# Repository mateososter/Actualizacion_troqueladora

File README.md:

# Actualizacion_troqueladora

Repositorio para la realizacion del proyecto para actualizar una troqueladora manual de mandibulas, agregando un display e identificación 
de usuarios por el método de tarjetas RFID.

Entorno a utilizar:   Keil uVision 5
Asistente:            CubeMX
Lenguaje principal:   c
Placa de desarrollo:  STM32F411

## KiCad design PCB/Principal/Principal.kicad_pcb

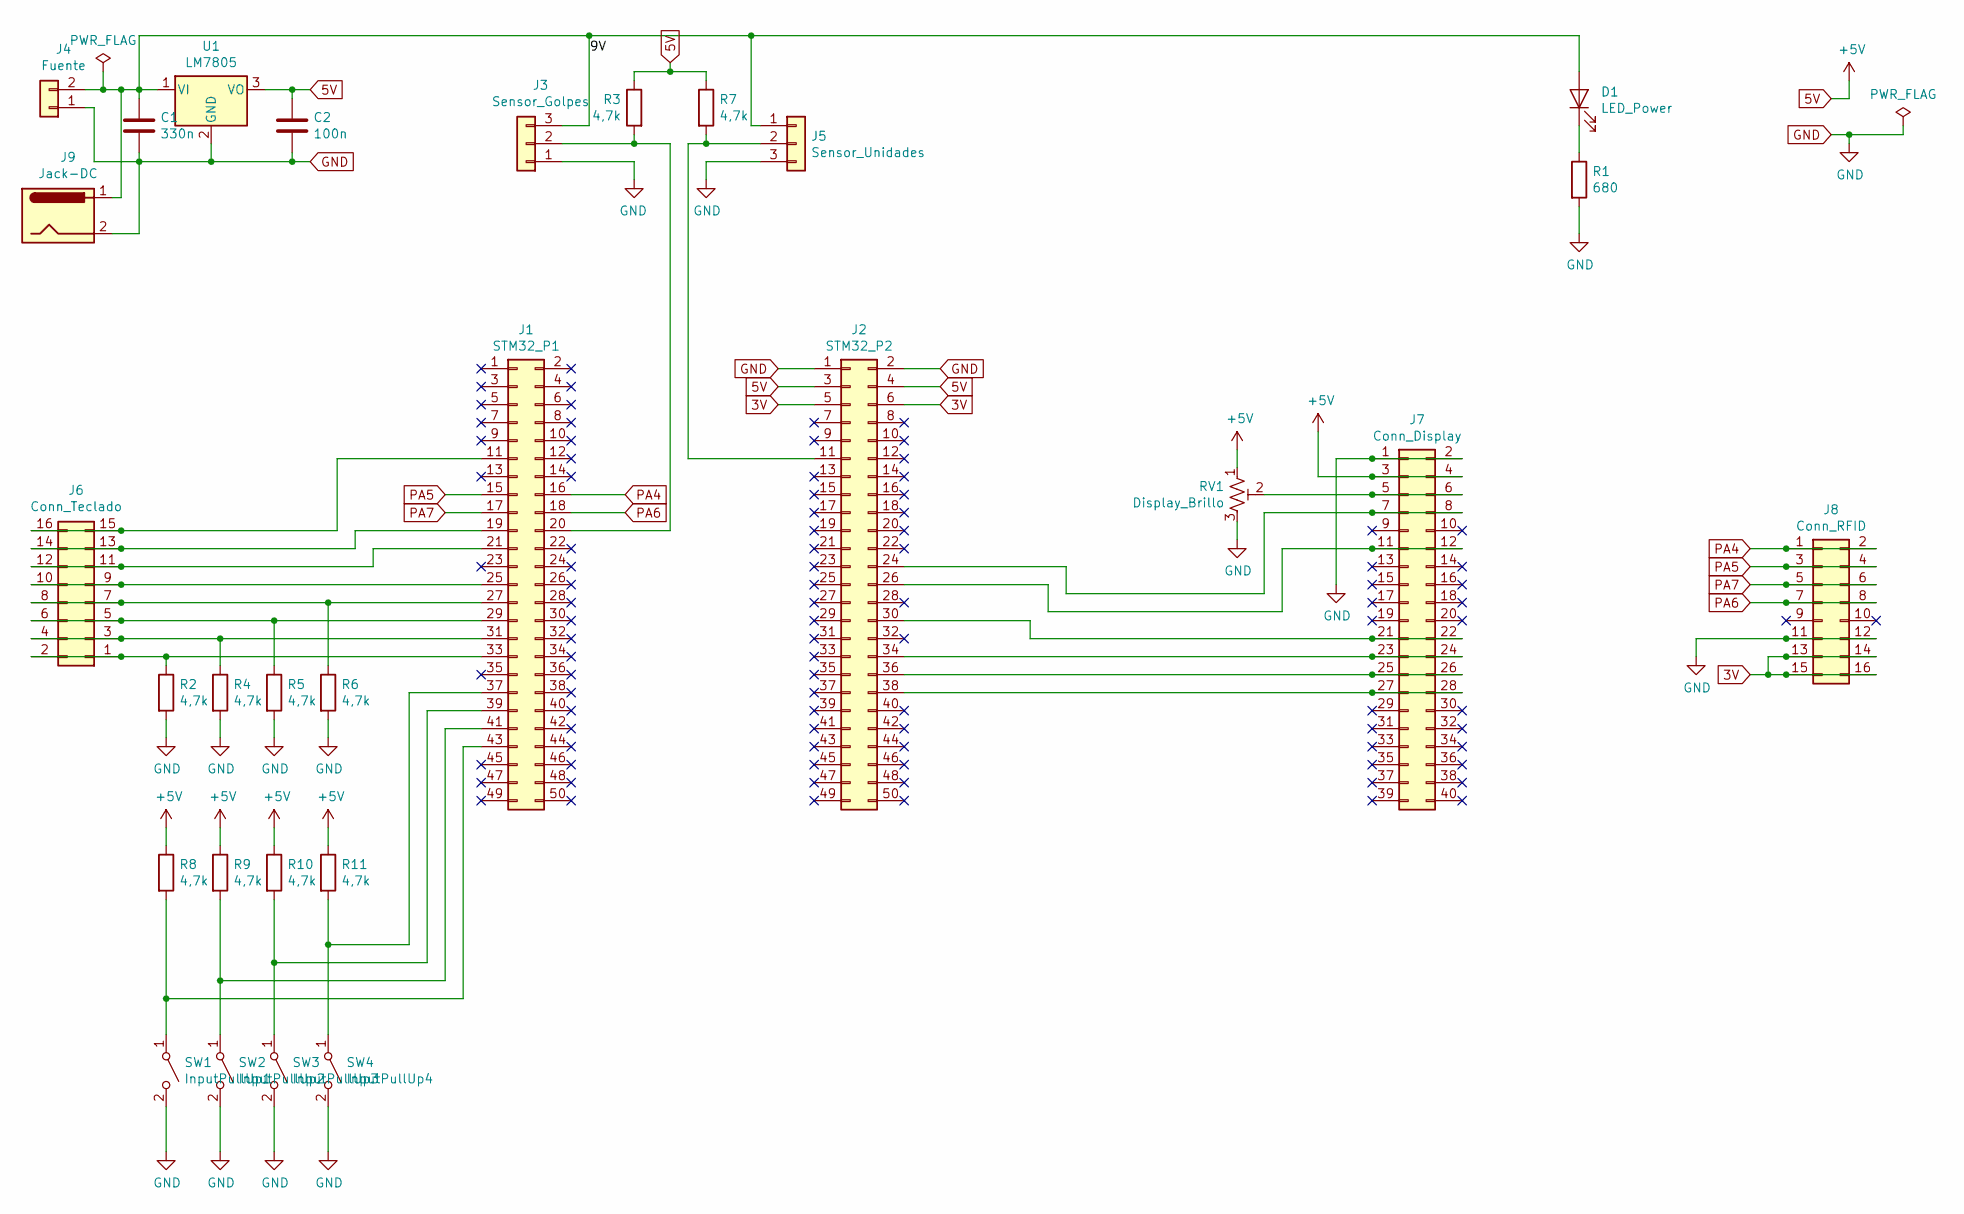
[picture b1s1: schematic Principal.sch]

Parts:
C1: 330n; C_Disc_D7.5mm_W2.5mm_P5.00mm
C2: 100n; C_Disc_D7.5mm_W2.5mm_P5.00mm
D1: LED_Power; LED_D5.0mm
J1: STM32_P1; PinHeader_2x25_P2.54mm_Vertical
J2: STM32_P2; PinHeader_2x25_P2.54mm_Vertical
J3: Sensor_Golpes; TerminalBlock_bornier-3_P5.08mm
J4: Fuente; TerminalBlock_bornier-2_P5.08mm
J5: Sensor_Unidades; TerminalBlock_bornier-3_P5.08mm
J6: Conn_Teclado; PinSocket_2x08_P2.54mm_Vertical
J7: Conn_Display; PinSocket_2x20_P2.54mm_Vertical
J8: Conn_RFID; PinSocket_2x08_P2.54mm_Vertical
J9: Jack-DC; BarrelJack_Horizontal
R1: 680; R_Axial_DIN0207_L6.3mm_D2.5mm_P10.16mm_Horizontal
R2, R3, R4, R5, R6, R7, R8, R9, R10, R11: 4,7k; R_Axial_DIN0207_L6.3mm_D2.5mm_P10.16mm_Horizontal
RV1: Display_Brillo; Potentiometer_Bourns_3266Y_Vertical
SW1: InputPullUp1; TerminalBlock_bornier-2_P5.08mm
SW2: InputPullUp2; TerminalBlock_bornier-2_P5.08mm
SW3: InputPullUp3; TerminalBlock_bornier-2_P5.08mm
SW4: InputPullUp4; TerminalBlock_bornier-2_P5.08mm
U1: LM7805; TO-220-3_Vertical

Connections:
3V: J2.5, J2.6, J8.13, J8.14, J8.15, J8.16
5V: C2.1, J2.3, J2.4, J7.3, J7.4, R3.1, R7.1, R8.1, R9.1, R10.1, R11.1, RV1.1, U1.3 (VO)
/9V: C1.1, D1.2 (A), J3.3, J4.2, J5.1, J9.1, U1.1 (VI)
GND: C1.2, C2.2, J2.1, J2.2, J3.1, J4.1, J5.3, J7.1, J7.2, J8.11, J8.12, J9.2, R1.2, R2.2, R4.2, R5.2, R6.2, RV1.3, SW1.2 (B), SW2.2 (B), SW3.2 (B), SW4.2 (B), U1.2 (GND)
unnamed: D1.1 (K), R1.1
unnamed: J1.11, J6.15, J6.16
unnamed: J1.19, J6.13, J6.14
unnamed: J1.20, J3.2, R3.2
unnamed: J1.21, J6.11, J6.12
unnamed: J1.25, J6.9, J6.10
unnamed: J1.27, J6.7, J6.8, R6.1
unnamed: J1.29, J6.5, J6.6, R5.1
unnamed: J1.31, J6.3, J6.4, R4.1
unnamed: J1.33, J6.1, J6.2, R2.1
unnamed: J1.37, R11.2, SW4.1 (A)
unnamed: J1.39, R10.2, SW3.1 (A)
unnamed: J1.41, R9.2, SW2.1 (A)
unnamed: J1.43, R8.2, SW1.1 (A)
unnamed: J2.11, J5.2, R7.2
unnamed: J2.24, J7.7, J7.8
unnamed: J2.26, J7.11, J7.12
unnamed: J2.30, J7.21, J7.22
unnamed: J2.34, J7.23, J7.24
unnamed: J2.36, J7.25, J7.26
unnamed: J2.38, J7.27, J7.28
unnamed: J7.5, J7.6, RV1.2
PA4: J1.16, J8.1, J8.2
PA5: J1.15, J8.3, J8.4
PA6: J1.18, J8.7, J8.8
PA7: J1.17, J8.5, J8.6

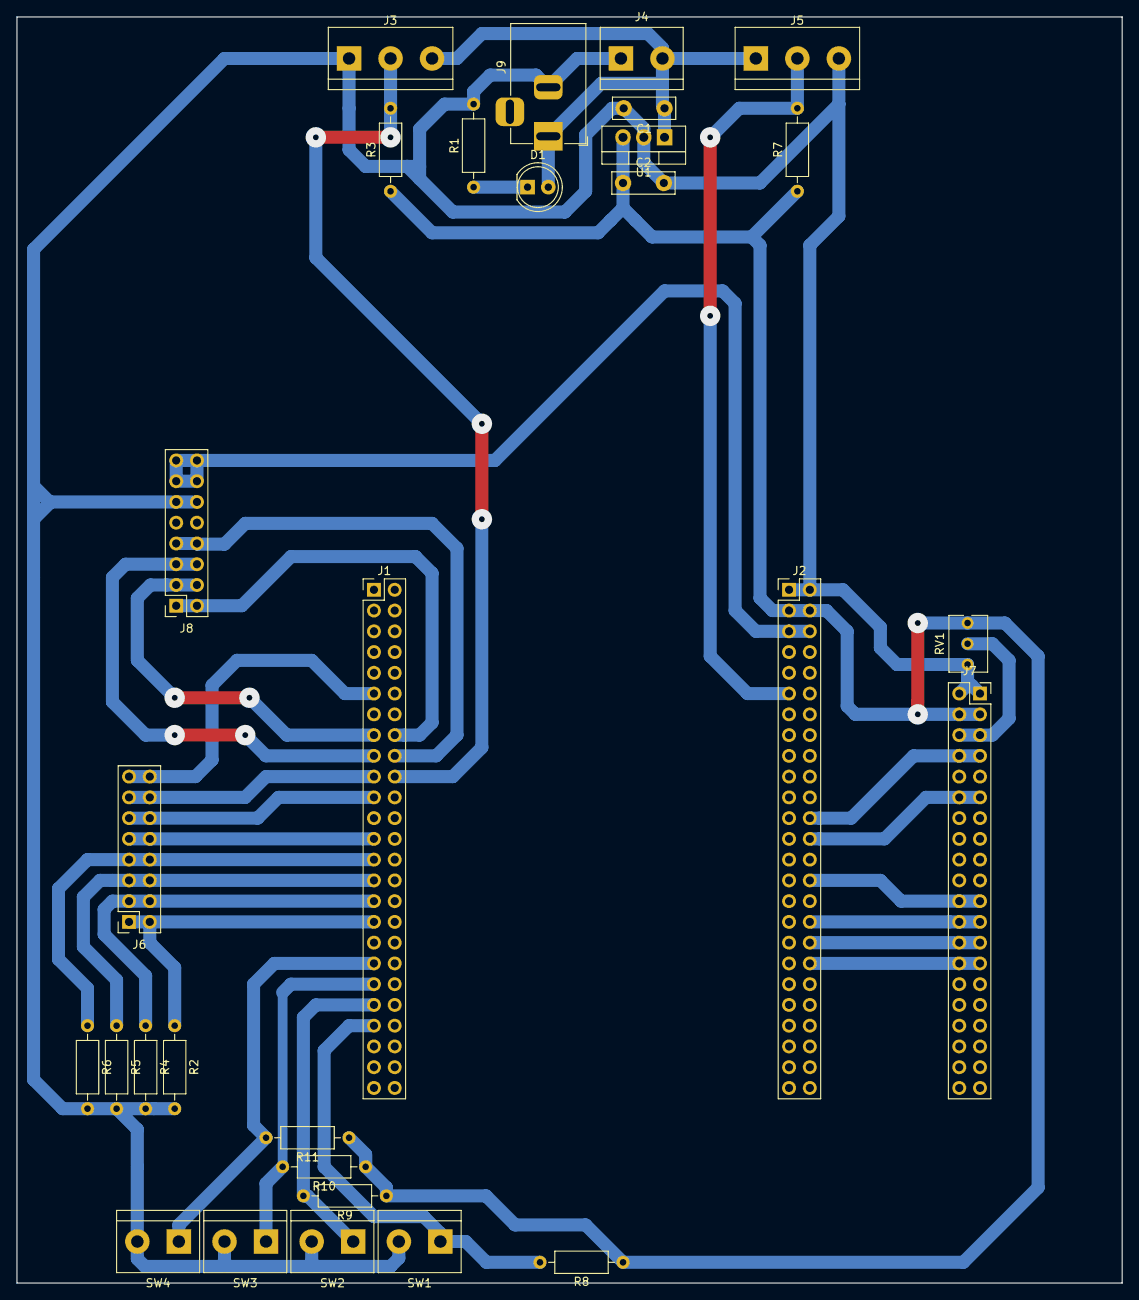
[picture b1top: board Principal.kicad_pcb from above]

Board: 2 copper layers, 135.3 x 154.9 mm, 29 parts (0 on the bottom side), 30 nets.

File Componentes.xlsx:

Ref | Componente | Valor | Tengo | Lista compras
C1 | Capacitor | 330n | ok | 2 Tira pines hembra a placa
C2 | Capacitor | 100n | ok | 2 IDC 16 macho a placa
D1 | LED | 5mm | ok | 1 IDC 40 macho a placa
J1 | Tira pines | Hembra a placa |  | 2 IDC 16 hembra a cable
J2 | Tira pines | Hembra a placa |  | 1 IDC 40 hembra a cable
J3 | Bornera | 3 | ok | 10 m Cable plano 20 vias
J4 | Bornera | 2 | ok | Jack DC
J5 | Bornera | 3 | ok | 10 R 680
J6 | IDC | 16 macho a placa |  | 20 R 4,7k
J7 | IDC | 40 macho a placa
J8 | IDC | 16 macho a placa
J9 | Jack DC
R1 | Resistencia | 680
R2 | Resistencia | 4,7k
R3 | Resistencia | 4,7k
R4 | Resistencia | 4,7k
R5 | Resistencia | 4,7k
R6 | Resistencia | 4,7k
R7 | Resistencia | 4,7k
R8 | Resistencia | 4,7k
R9 | Resistencia | 4,7k
R10 | Resistencia | 4,7k
R11 | Resistencia | 4,7k
RV1 | Trimmer | 10k | ok
SW1 | Bornera | 2 | ok
SW2 | Bornera | 2 | ok
SW3 | Bornera | 2 | ok
SW4 | Bornera | 2 | ok
U1 | Regulador | LM7805 | ok

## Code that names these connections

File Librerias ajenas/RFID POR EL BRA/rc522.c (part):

// Mifare RC522 RFID Card reader 13.56 MHz

// MFRC522		STM32F103		DESCRIPTION
// CS (SDA)		PA4					SPI1_NSS	Chip select for SPI
// SCK				PA5					SPI1_SCK	Serial Clock for SPI
// MOSI				PA7 				SPI1_MOSI	Master In Slave Out for SPI
// MISO				PA6					SPI1_MISO	Master Out Slave In for SPI
// IRQ				-						Irq
// GND				GND					Ground
// RST				3.3V				Reset pin (3.3V)
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
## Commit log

2018-08-27 Descripcion inicial
2018-08-27 Archivillos
    Presentación del proyecto y hoja de datos del lector de tarjetas, con Highligts
2018-08-31 Diagramas preliminares
2018-09-01 Primera version de codigo
    Probando timer us
2018-09-15 Archivos base arduino
    Llegue hasta Writeregister, hay que seguir migrando
2018-09-21 Migrando libreria de arduino
2018-09-27 Librería bajada de stm
    No está incluida en el proyecto ni nada
2018-09-28 Actualizacion del preinforme
2018-10-24 Mensajes del display
    Digamos que podría ser la estructura final del menú.
2018-10-26 Mergeando los excel
2018-11-02 Arrancamos con la logica
    Prueba de interrupciones externas, programacion del menu principal.
2018-11-05 ANDA EL DISPLAY
    En actualizacion_troqueladora esta la rutina del display y estan cargados los mensajes del menu principal. Esta implementado con un timer de us bloqueante, data paralela en el display y nada mas.
    Tambien se agrega la seccion Lector en la cual esta la prueba del lector de RFID sin embargo no lo pude probar por la falta de tags de 125kHz
2018-11-09 TEclado
    En la seccion logica arranca la configuracion del teclado.
2018-11-10 El teclado ya reconoce cada tecla
    Lo proximo seria integrar el tecladito que esta en Logica con el menu que esta en actualizacion troqueladora. Va queriendo...
2018-12-05 Avances generales
    Prueba de todos modulos en un solo cube. porque habia tirado problemas para mezclar el teclado con el display
2018-12-07 Hay que invertir la logica de las interrupciones
    Para poder ponerle las pullup que son la que va. Los sensores andan piola con la logica inversa y un pullup. Las interrupciones si las configuras directo desde el cube andan bien, algo hay oculto.
2018-12-07 En el display se ven las unidades
    Falta revisar el teclado que onda
2019-01-07 Creacion del PCB
    Cambie unas cosas por comodidad en la placa. Chequear en el programa
2019-01-08 Alta plaquita guacho
    Hay que acomodarla pero no quedo ningun puente.
    Cambie TODOS los GPIO. Atento.
2019-01-12 Aca no me acuerdo que hice....
2019-01-13 ALTA PLACA GUACHO
    Nada, eso.
2019-01-15 Gerber y pdfs
2019-01-16 Acomodado el cube de "final"
    Ya esta todo listo para empezar a programar posta.
2019-01-25 Creación del menú
    El menú principal en función del botón que apretado y la posición actual del menú.
2019-02-15 Varios
2019-03-14 Backup
    Avances en el programa, falta probar el lector de RFID, estoy re colgado con eso. Subo la versión pq voy a hacer un backup nomas.
2019-04-04 LA puta madre
    Al probar la placa terminada me encontré con que el sensor inductivo necesita más tensión para andar bien. Lo cual es medio una garcha. Solucion posible: fuente de 12 con regulador de 5. Achurar la p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
2019-04-11 Bueno, bien.
    3 problemas corregidos.
    1. Falso contacto+corto en la placa
    2. Mala conexión del LCD (cables de datos cruzados).
    3. Soft: La cantidad de unidades no se veía porque la función sprintf no estaba funcionando con un puntero a char, por lo que tuve que escribirla como un vector de char, ahí anduvo re piola.
2019-06-01 Prueba teclado
    Las teclas ene l modo interrupcion no andaban del todo bien, ahora probe un metodo hibrido, pero sino anda hay que encuestarlo en el main.
2019-06-14 Teclado OK
    Bueno, el teclado funciona, método encuesta, así que quedará pendiente para algún momento descubrir por qué las interrupciones no funcionaban.
    Por otro lado, el lector UART no anda. Lo probé con un osciloscopio y la salida no escupe ningún dato. Voy a probar con el clásico SPI. Aún no descarté que los llaveros sean de otra frecuencia.
2019-06-18 Chau RDM6300
    Decidí cambiar el RDM6300 por el viejo y confiable MFRC522. El cacharro UART no hace NADA, lo probe con el osciloscopio y no escupe ningun dato por el tx, por lo tanto, lo voy a descartar, el otro es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
2019-06-21 Migracion de librerias de RFID
    La onda es ir transcribiendo funcion por funcion... que va a ser...
2019-06-24 0 Errors.
    Casi toda la libreria esta transcripta. Falta la funcion compare nada mas. Pero al compilar no dio ningun error y pareciera estar todo en orden.
    Esperemo.
2019-06-24 Hay que probar bien
    Listas las conexiones, Se alimenta con 5V.
    Ademas agregue la libreria del brayan a la carpeta
2019-08-14 Corregido error en lectura de registros SPI
    Armar un proyecto nuevo en "Lector" y hacer andar el modulo con las librerías que vienen del 522. Despues migrar al Final.
2019-08-30 Seguimo en la nebulosa
    Probar el RFID tal cual está.
2019-09-20 Avance en el informe
2019-09-28 Anda el RFID
    Listo el reconocimiento de tarjetas. Ahora hay que terminar detalles del funcionamiento y ya estamos.
2019-09-28 Anda el RFID
    Listo el reconocimiento de tarjetas. Ahora hay que terminar detalles del funcionamiento y ya estamos.
    AL final use una libreria de un guachin y listo.
2019-10-08 Sumando cambios al PCB
    Se agrego al esquematico fuente de 5V con 7805 y la conexion del rfid.
2019-10-11 Fin esquematico.
    Ahora falta PCB
2019-10-16 Fin PCB re piola
2019-10-22 Lo mismo de abajo
2019-10-23 Avance en el programa principal
2019-10-25 Continuación del informe.
    Agregado de pines I2C para la memoria al archivo de pines
2019-10-31 Muchos avances en el código
    1-Inclusión de la librería MY_FLASH que es para escribir datos no volátiles.
    2- El menú de Agregar operario anda excelente, incluso la introducción de nombre de operario.
    3- Los submenús Operarios y Productividad ya recorren para un lado y para el otro los operarios cargados en el sistema. Faltaría mostrar más elegantemente el ID tarjeta.
2019-11-14 Lectura y guardado en memoria FLASH
    La flash tiene bastantes inconvenientes, pero bueno, es no volatil.
    La idea es que cuando se escriba, escribir todo el mapa de memoria que defini, porque sino hay problemas con los bits que no se escriben. No hay que abusar de esta funcion ya que el numero de escritu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
2019-11-21 VAMO GUACHO
    Idealmente "Ultima" version del codigo.
    Anda todo y anda muy bien. funciona autonomo sin problemas.
2019-12-03 Avances de informe final
2019-12-03 Auto stash before merge of "master" and "origin/master"
2019-12-03 Avance informe
2019-12-04 Avance de diagramas
2019-12-04 Falta poquitoooo
2020-01-25 Informe final completo.
2020-09-04 Agregado de display secundario y boton de descuento
    Se agrega comunicación UART para repetir la indicación de unidades en un display secundario más grande para facilitar la visión del operario. Además se agrega un botón que permite descontar una unida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
2021-01-28 Cotizacion de componentes
